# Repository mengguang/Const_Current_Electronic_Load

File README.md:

# Const_Current_Electronic_Load
A very simple const current electronic load using mosfet and opamp.

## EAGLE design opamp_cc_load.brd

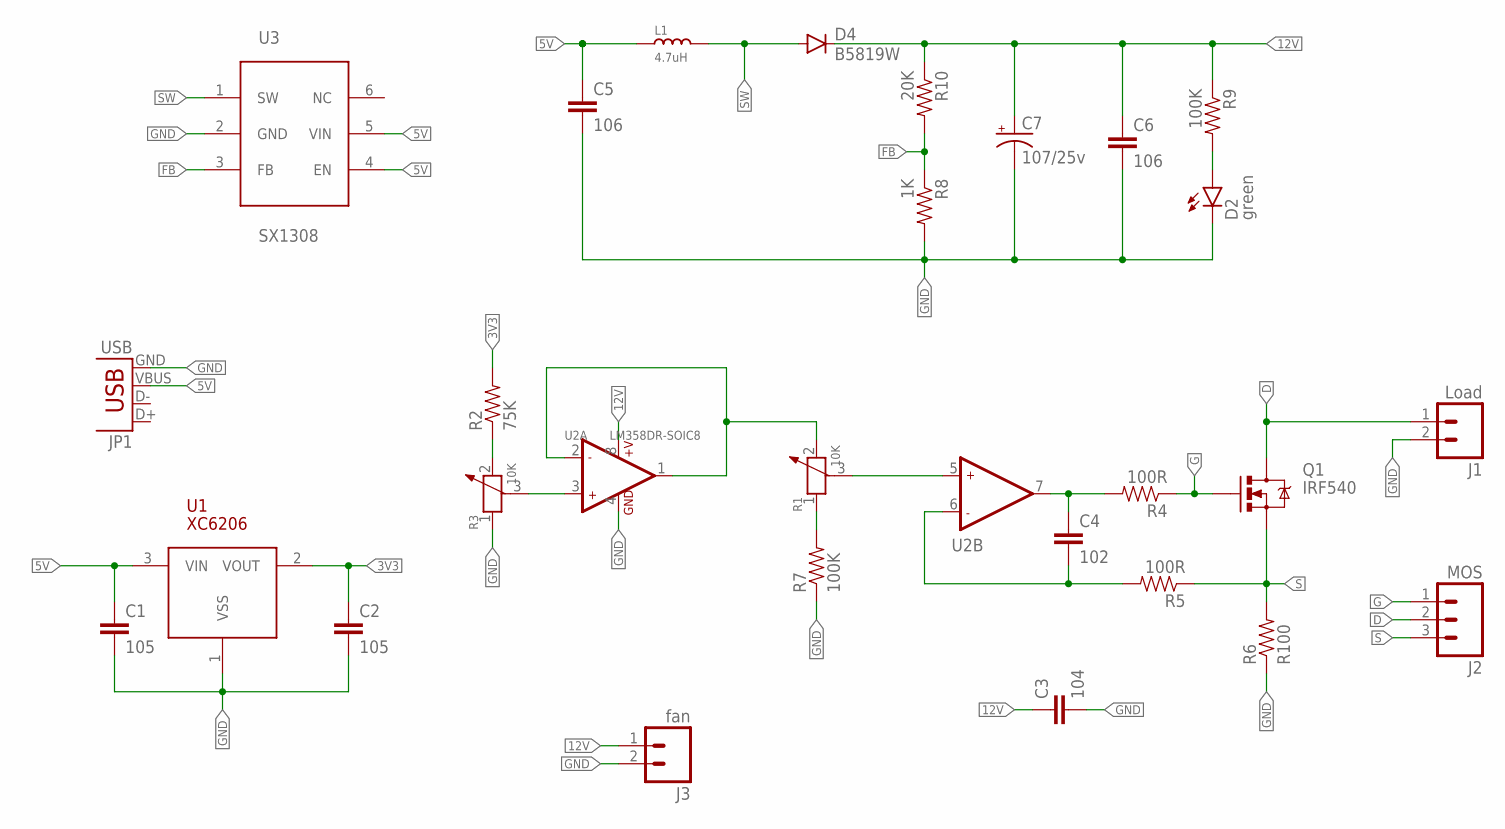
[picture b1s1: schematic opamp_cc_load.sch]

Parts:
C1, C2: 105; 0603-CAP
C3: 104; 0603-CAP
C4: 102; 0603-CAP
C5, C6: 106; 1206
C7: 107/25v; CPOL-RADIAL-100UF-25V
D2: green; LED-0603-SEEED
D4: B5819W; SOD-123
J1: Load; SCREWTERMINAL-5MM-2
J2: MOS; SCREWTERMINAL-5MM-3
J3: fan; 1X02_NO_SILK
JP1: USB; MICROUSB-U-F-M5DD-Y-1
L1: 4.7uH; SMD-2P-5.0X5.0X2.0MM
Q1: IRF540; TO220V
R1, R3: 10K; ADJR3-7.0X7.0X5.0MM
R2: 75K; 0603-RES
R4, R5: 100R; 0603-RES
R6: R100; R2512
R7, R9: 100K; 0603-RES
R8: 1K; 0603-RES
R10: 20K; 0603-RES
U1: XC6206; SOT23-3
U2: LM358DR-SOIC8; SOIC8-1.27-5X4MM
U3: SX1308; SOT23-6

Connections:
3V3: C2.1, R2.2, U1.2 (VOUT)
5V: C1.1, C5.1, JP1.VBUS, L1.1, U1.3 (VIN), U3.4 (EN), U3.5 (VIN)
12V: C3.1, C6.1, C7.1 (+), D4.C, J3.1, R9.1, R10.1, U2.8 (+V)
D: J1.1, J2.2, Q1.2 (D)
FB: R8.1, R10.2, U3.3 (FB)
G: J2.1, Q1.1 (G), R4.1
GND: C1.2, C2.2, C3.2, C5.2, C6.2, C7.2 (-), D2.- (C), J1.2, J3.2, JP1.GND, R3.1, R6.1, R7.1, R8.2, U1.1 (VSS), U2.4 (GND), U3.2 (GND)
unnamed: R3.3 (2), U2.3 (+IN1)
unnamed: R1.2 (3), U2.1 (OUT1), U2.2 (-IN1)
unnamed: C4.1, R4.2, U2.7 (OUT2)
unnamed: D2.+ (A), R9.2
unnamed: R2.1, R3.2 (3)
unnamed: C4.2, R5.2, U2.6 (-IN2)
unnamed: R1.3 (2), U2.5 (+IN2)
unnamed: R1.1, R7.2
S: J2.3, Q1.3 (S), R5.1, R6.2
SW: D4.A, L1.2, U3.1 (SW)

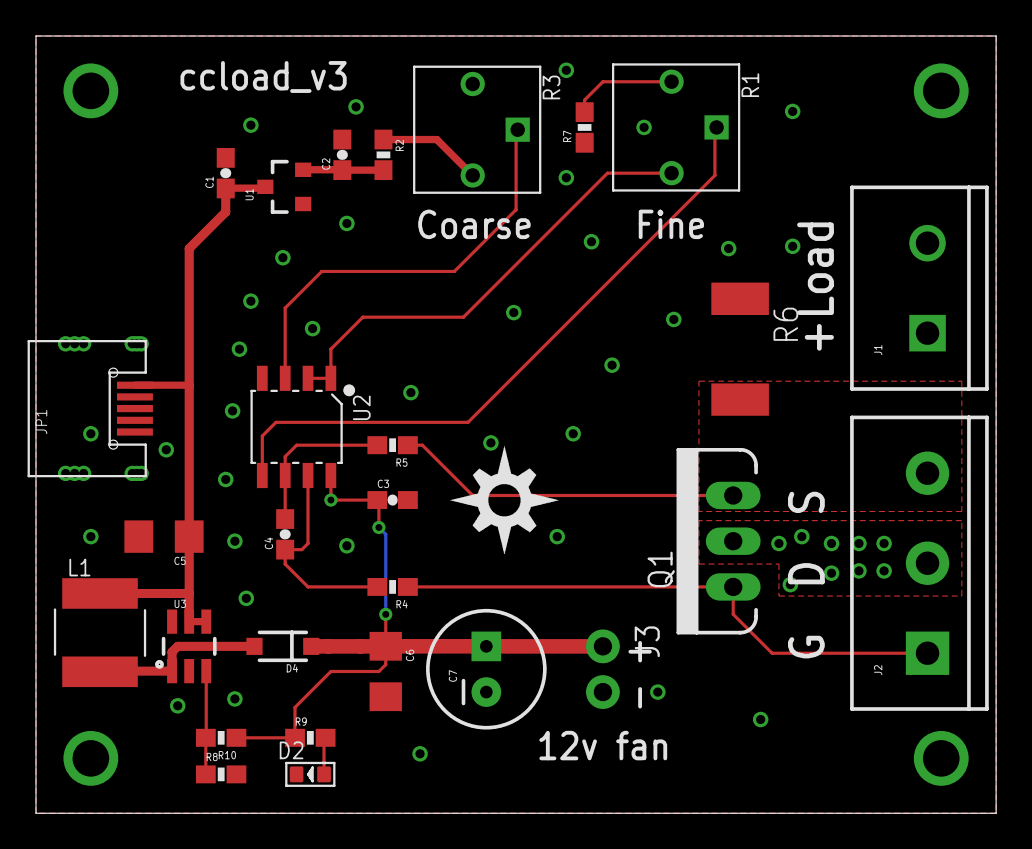
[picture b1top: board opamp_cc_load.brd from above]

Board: 2 copper layers, 53.3 x 43.2 mm, 29 parts (0 on the bottom side), 17 nets.

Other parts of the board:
U$1: DIYNOVA_LOGO

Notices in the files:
parts and their libraries:
SparkFun-Connectors: Licensing: Creative Commons ShareAlike 4.0 International - https://creativecommons.org/licenses/by-sa/4.0
